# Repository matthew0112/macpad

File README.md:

# Macpad

**This macropad has 8 switches, a roatary encoder, OLED Display, 12 LEDs surrounding the keys**

The extra header allows the ablity to connect more devices in the future, with custom firmware, as it uses an I²C bus

## Schematic
Made in [KiCAD](https://www.kicad.org/)

## PCB
Also made in [KiCAD](https://www.kicad.org/)

## Case
Made with [Onshape](https://www.onshape.com/en/)
[View the Onshape Project](https://cad.onshape.com/documents/a3063f954316ced9d12dc1eb/w/765bffe99711a4a00266f054/e/551ffca8c70dbb2c958da650)

## BOM
- 1 Seeed XIAO
- 9x through-hole 1N4148 Diodes
- 8x MX-Style switches
- 1 Rotary encoder
- 1 OLED display
- 8x white blank DSA keycaps
- 12x SK6812 MINI-E LEDs
- 4x M3x16mm screws

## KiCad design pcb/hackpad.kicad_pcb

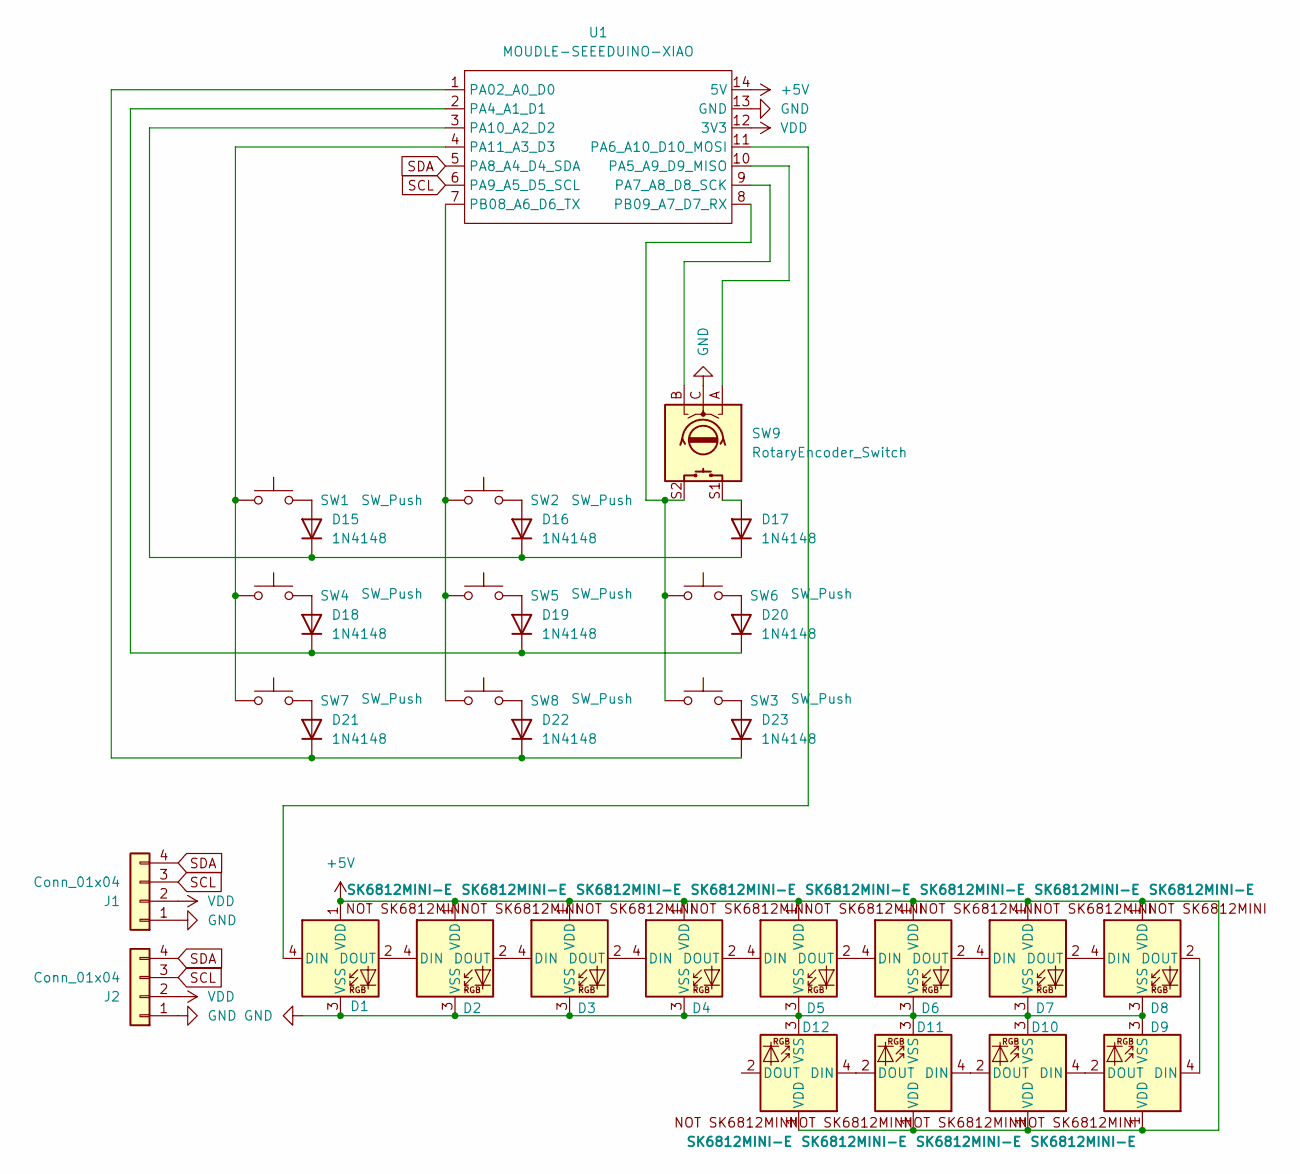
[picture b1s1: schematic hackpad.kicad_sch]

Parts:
D1, D2, D3, D4, D5, D6, D7, D8, D9, D10, D11, D12: SK6812MINI-E; SK6812MINI-E_fixed
D15, D16, D17, D18, D19, D20, D21, D22, D23: 1N4148; D_DO-35_SOD27_P7.62mm_Horizontal
J1: Conn_01x04; SSD1306-0.91-OLED-4pin-128x32
J2: Conn_01x04; PinHeader_1x04_P2.54mm_Vertical
SW1, SW2, SW3, SW4, SW5, SW6, SW7, SW8: SW_Push; SW_Cherry_MX_1.00u_PCB
SW9: RotaryEncoder_Switch; RotaryEncoder_Alps_EC11E-Switch_Vertical_H20mm
U1: MOUDLE-SEEEDUINO-XIAO; XIAO-Generic-Hybrid-14P-2.54-21X17.8MM

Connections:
+5V: D1.1 (VDD), D2.1 (VDD), D3.1 (VDD), D4.1 (VDD), D5.1 (VDD), D6.1 (VDD), D7.1 (VDD), D8.1 (VDD), D9.1 (VDD), D10.1 (VDD), D11.1 (VDD), D12.1 (VDD), U1.14 (5V)
GND: D1.3 (VSS), D2.3 (VSS), D3.3 (VSS), D4.3 (VSS), D5.3 (VSS), D6.3 (VSS), D7.3 (VSS), D8.3 (VSS), D9.3 (VSS), D10.3 (VSS), D11.3 (VSS), D12.3 (VSS), J1.1, J2.1, SW9.C, U1.13 (GND)
unnamed: D1.4 (DIN), U1.11 (PA6_A10_D10_MOSI)
unnamed: D1.2 (DOUT), D2.4 (DIN)
unnamed: D2.2 (DOUT), D3.4 (DIN)
unnamed: D3.2 (DOUT), D4.4 (DIN)
unnamed: D4.2 (DOUT), D5.4 (DIN)
unnamed: D5.2 (DOUT), D6.4 (DIN)
unnamed: D6.2 (DOUT), D7.4 (DIN)
unnamed: D7.2 (DOUT), D8.4 (DIN)
unnamed: D8.2 (DOUT), D9.4 (DIN)
unnamed: D9.2 (DOUT), D10.4 (DIN)
unnamed: D10.2 (DOUT), D11.4 (DIN)
unnamed: D11.2 (DOUT), D12.4 (DIN)
unnamed: D15.2 (A), SW1.2
unnamed: D15.1 (K), D16.1 (K), D17.1 (K), U1.3 (PA10_A2_D2)
unnamed: D16.2 (A), SW2.2
unnamed: D17.2 (A), SW9.S1
unnamed: D18.2 (A), SW4.2
unnamed: D18.1 (K), D19.1 (K), D20.1 (K), U1.2 (PA4_A1_D1)
unnamed: D19.2 (A), SW5.2
unnamed: D20.2 (A), SW6.2
unnamed: D21.2 (A), SW7.2
unnamed: D21.1 (K), D22.1 (K), D23.1 (K), U1.1 (PA02_A0_D0)
unnamed: D22.2 (A), SW8.2
unnamed: D23.2 (A), SW3.2
unnamed: SW9.A, U1.10 (PA5_A9_D9_MISO)
unnamed: SW9.B, U1.9 (PA7_A8_D8_SCK)
unnamed: SW1.1, SW4.1, SW7.1, U1.4 (PA11_A3_D3)
unnamed: SW2.1, SW5.1, SW8.1, U1.7 (PB08_A6_D6_TX)
unnamed: SW3.1, SW6.1, SW9.S2, U1.8 (PB09_A7_D7_RX)
SCL: J1.3, J2.3, U1.6 (PA9_A5_D5_SCL)
SDA: J1.4, J2.4, U1.5 (PA8_A4_D4_SDA)
VDD: J1.2, J2.2, U1.12 (3V3)

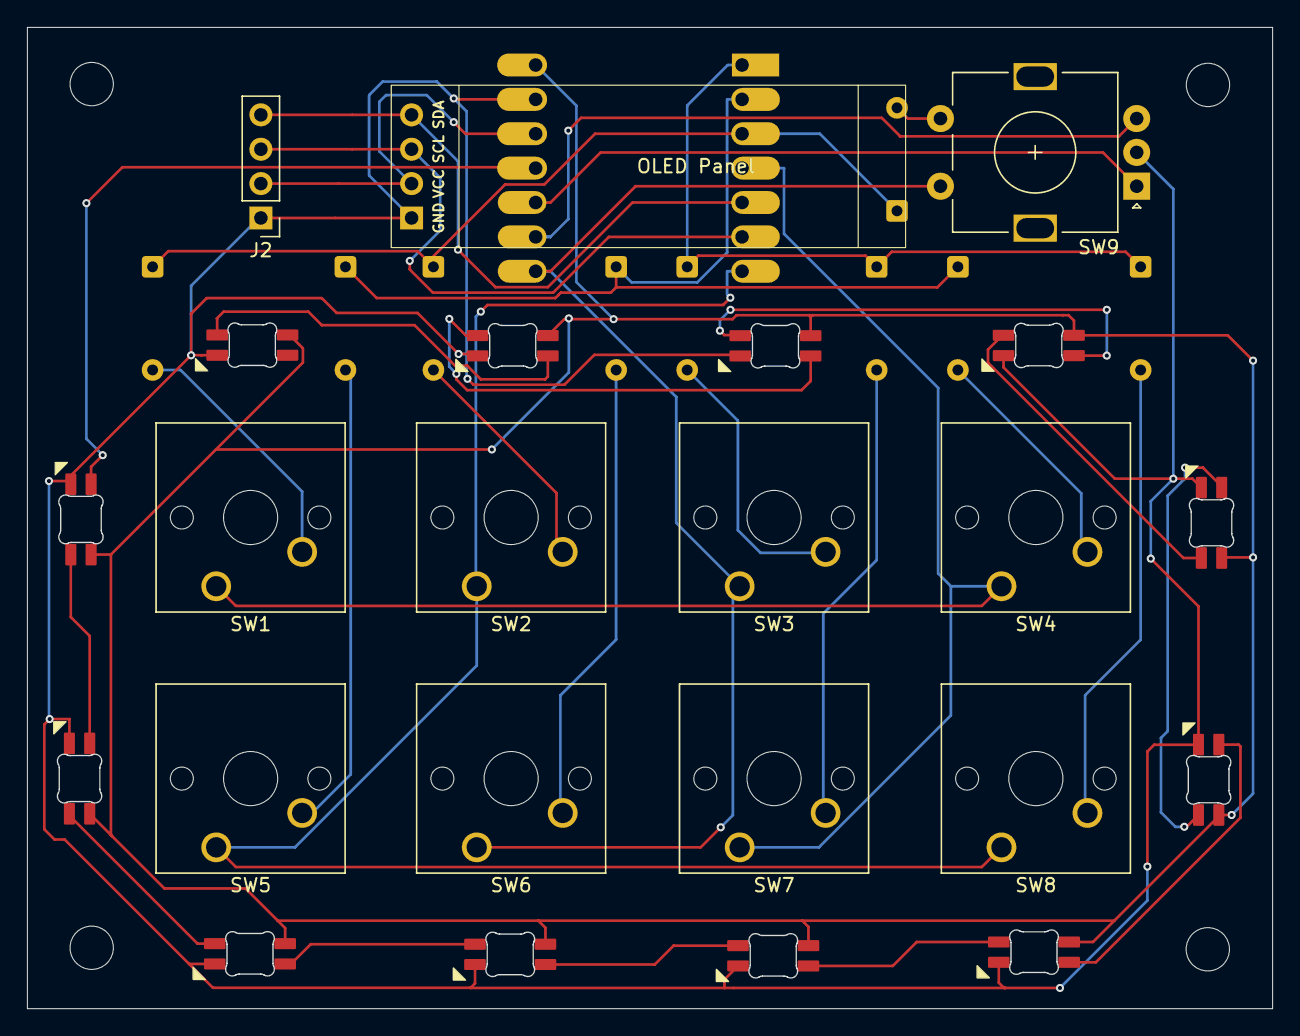
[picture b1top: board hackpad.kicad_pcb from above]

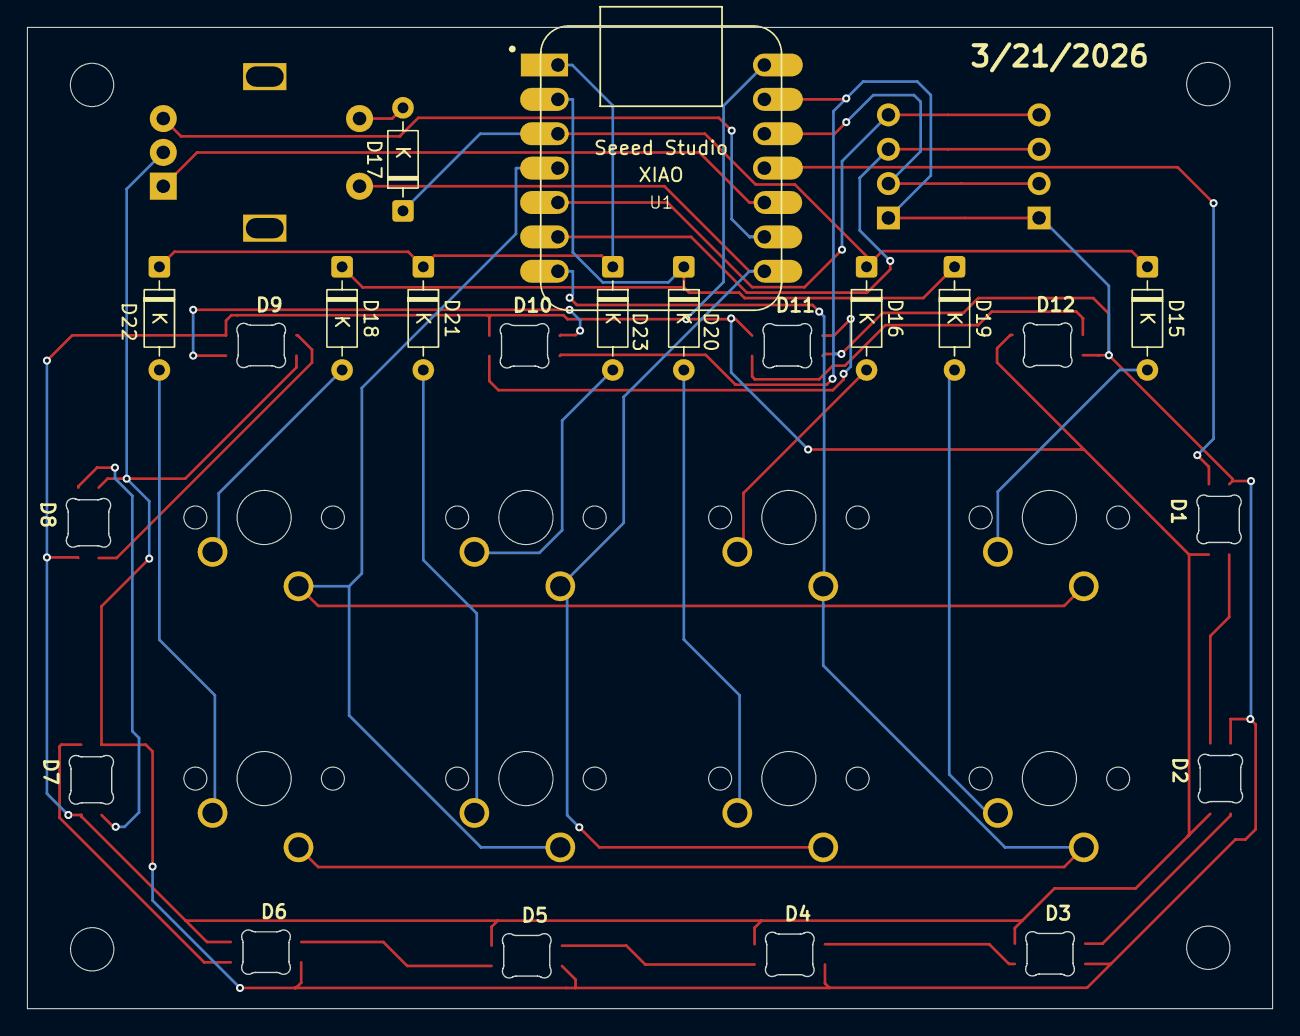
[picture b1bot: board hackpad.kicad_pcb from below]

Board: 2 copper layers, 92.0 x 72.5 mm, 33 parts (22 on the bottom side), 34 nets.

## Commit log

2026-03-22 macpad
2026-03-22 README
2026-03-28 Onshape CAD Source files
